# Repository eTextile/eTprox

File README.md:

# eTprox
## eTextile Proximity Switch

### Credits
- **Wendy Van Wynsberghe** <wendy[AT]constantvzw.org>
- **License** : Cern Open Hardware (see the License file)
- **wenPage** : http://etextile-summercamp.org/swatch-exchange/sewable-proximity-switch-board-1/
- **Repository**: https://github.com/eTextile/eTprox/tree/master

### The story
"What happens when you have been working with tactile textile and touch in this era, where transmission of viral particles is a hot topic? Working with the MPR121 board? You stop and think it over. During the hard lockdown in May I started to think about tactility and proximity, activating without touching. I could not imagine a public touching the installation I was building. I researched already existing boards and possibilities and I didn’t find what I wanted. I dove into the realms of all kinds of chips and circuits. Infrared, ultrasonic, time of flight – they are all sensors that handle proximity and distance but they do not turn your conductive textile into a tactile interactive object. My second find was bingo: the MTCH101 chip, is a switch, that means it turns something on and off, it makes your conductive textile into a button by hovering over it. In the words of the company that makes them: the MTCH101 is a low cost single channel capacitive proximity detector. The distance of activation and the sensitivity depends on the voltage you give it and the surface of your conductive antenna. The activation can even happen with a non conductive layer covering it. If the switch has a temporary glitch, it recalibrates itself very fluently."

## BOM
- PCB with SMD components
- eTextile antenna (conductive thread or conductive textile)
- Microcontroller (not included)

| Référence                | Def (Kicad components names)                  | Quantity | Value   |
|:-------------------------|:----------------------------------------------|----------|:--------|
|  J2	                   | JST_XH_S3B-XH-A_1x03_P2.50mm_Horizontal	   |    1     |         |
|  RV1	                   | Potentiometer_Vishay_TS53YJ_Vertical	       |    1	  | 10K     |
|  U1	                   | SOT-23-6_Handsoldering	                       |    1	  | MTCH101 | 
|  D1	                   | LED_0805_2012Metric_Pad1.15x1.40mm_HandSolder |    1	  | LED     |
|  C1	                   | C_0805_2012Metric_Pad1.18x1.45mm_HandSolder   |    1	  | 0.1µF   |
|  R7,R3	               | R_0805_2012Metric_Pad1.20x1.40mm_HandSolder   |    2	  | 4.7K    |
|  R6	                   | R_0805_2012Metric_Pad1.20x1.40mm_HandSolder   |    1	  | 1K      |
|  R5,R4	               | R_0805_2012Metric_Pad1.20x1.40mm_HandSolder   |    2	  | 10K     |

## Credits
Design forked from Knottex project @ Timelab.

# TODO
- See : http://www.farnell.com/datasheets/1714150.pdf

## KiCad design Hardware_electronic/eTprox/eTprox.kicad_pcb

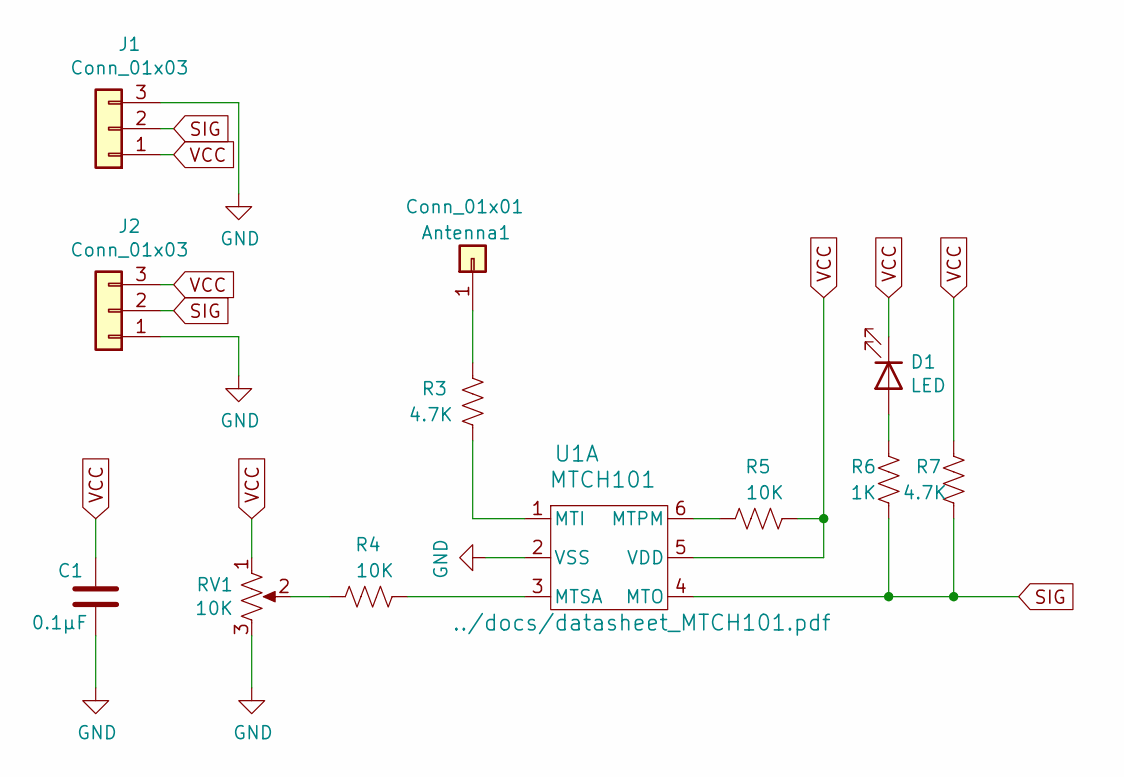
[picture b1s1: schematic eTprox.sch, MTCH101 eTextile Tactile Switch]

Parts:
Antenna1: Conn_01x01; eTprox_Pad_1x01
C1: 0.1µF; C_0805_2012Metric_Pad1.18x1.45mm_HandSolder
D1: LED; LED_0805_2012Metric_Pad1.15x1.40mm_HandSolder
J1: Conn_01x03; eTprox_Pad_1x03
J2: Conn_01x03; JST_XH_S3B-XH-A_1x03_P2.50mm_Horizontal
R3, R7: 4.7K; R_0805_2012Metric_Pad1.20x1.40mm_HandSolder
R4, R5: 10K; R_0805_2012Metric_Pad1.20x1.40mm_HandSolder
R6: 1K; R_0805_2012Metric_Pad1.20x1.40mm_HandSolder
RV1: 10K; Potentiometer_Vishay_TS53YJ_Vertical
U1: MTCH101; SOT-23-6_Handsoldering

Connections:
GND: C1.2, J1.3, J2.1, RV1.3, U1.2 (VSS)
unnamed 1: Antenna1.1, R3.1; also elsewhere on the board
unnamed: D1.2 (A), R6.1
unnamed: R3.2, U1.1 (MTI)
unnamed: R4.1, RV1.2
unnamed: R4.2, U1.3 (MTSA)
unnamed: R5.1, U1.6 (MTPM)
SIG: J1.2, J2.2, R6.2, R7.2, U1.4 (MTO)
VCC: C1.1, D1.1 (K), J1.1, J2.3, R5.2, R7.1, RV1.1, U1.5 (VDD)

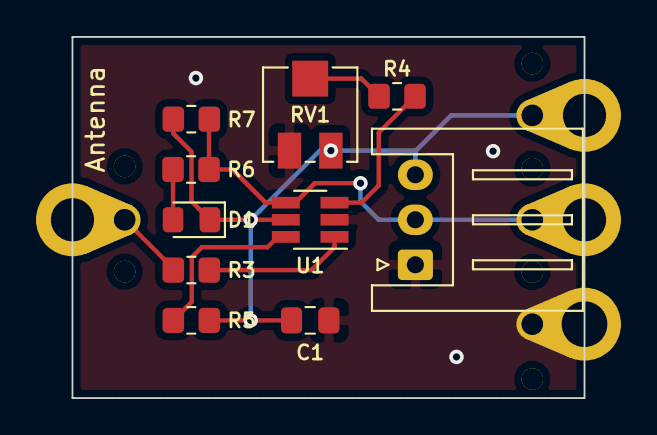
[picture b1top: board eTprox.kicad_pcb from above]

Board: 2 copper layers, 28.4 x 20.1 mm, 12 parts (0 on the bottom side), 9 nets.

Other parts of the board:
Antenna: Conn_01x01; eTprox_Pad_1x01

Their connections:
unnamed 1: Antenna.1; also elsewhere on the board

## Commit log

2021-04-27 Added JST plug
2021-04-27 Added polarity
2021-04-27 Added credits
2021-04-27 Minor changes
2021-04-27 Added BOM
2021-04-27 Added picture & 3D trimpot

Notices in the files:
Hardware_electronic/eTprox/eTprox.kicad_pcb:
License: CERN Open Hardware License
CERN OHL
